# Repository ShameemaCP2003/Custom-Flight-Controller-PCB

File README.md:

# Custom Flight Controller PCB

Open-source STM32-based flight controller designed in KiCad for PX4 and ArduPilot-compatible UAV platforms.

---

## Overview

This project is a custom flight controller developed from scratch as a learning and engineering exercise in embedded hardware design, sensor integration, power management, and PCB development.

The design is inspired by modern flight controller architectures and incorporates a high-performance STM32 microcontroller, onboard inertial sensors, environmental sensing, multiple communication interfaces, and PWM outputs for UAV control applications.

---

## Features

- STM32F446RET6 ARM Cortex-M4 MCU
- ICM-42670-P 6-Axis IMU
- BMP390 Barometric Pressure Sensor
- USB Type-C Interface
- CAN Bus Support
- Multiple UART Interfaces
- Dual SPI Interfaces
- ADC Inputs
- GPIO Expansion
- 6 Servo/PWM Outputs
- SWD Programming Interface
- Onboard 3.3V Regulation
- Power Protection Circuitry

---

## Hardware Specifications

| Component | Part Number |
|------------|------------|
| MCU | STM32F446RET6 |
| IMU | ICM-42670-P |
| Barometer | BMP390 |
| Voltage Regulator | SPX3819 |
| Crystal | 3.2mm × 2.5mm |
| USB Interface | USB Type-C |

---

## Communication Interfaces

| Interface | Quantity |
|------------|----------|
| CAN Bus | 1 |
| UART | 3 |
| SPI | 2 |
| ADC | 2 |
| GPIO Input | 1 |
| GPIO Output | 2 |

---

## PWM Outputs

| Output |
|----------|
| Servo 1 |
| Servo 2 |
| Servo 3 |
| Servo 4 |
| Servo 5 |
| Servo 6 |

---

## PCB Statistics

| Parameter | Value |
|------------|---------|
| Layers | 2 |
| Nets | 79 |
| Pads | 291 |
| Vias | 297 |
| Unrouted Nets | 0 |
| ERC Status | Passed |
| DRC Status | Passed |

---

## Design Workflow

1. Requirements Definition
2. Component Selection
3. Schematic Design
4. ERC Validation
5. PCB Placement
6. PCB Routing
7. Ground Plane Implementation
8. DRC Verification
9. Prototype Preparation

---

## Current Status

- ✅ Schematic Complete
- ✅ PCB Layout Complete
- ✅ ERC Passed
- ✅ DRC Passed
- ⏳ Prototype Manufacturing Pending
- ⏳ Hardware Bring-Up Pending
- ⏳ PX4 Integration Pending

---

## Future Improvements

Planned future revisions include:

- Dual redundant IMU architecture
- SD card logging
- Additional CAN interfaces
- GPS connector
- Battery management system
- Power monitoring enhancements
- 4-layer PCB revision
- PX4 board support package
- ArduPilot board support package

---

## Repository Structure

hardware/
├── schematic/
└── pcb/

docs/
└── images/

firmware/

---

## Acknowledgements

This project was created as a learning and engineering exercise in custom flight controller design.

The development process was heavily influenced by the open-source embedded systems community, including the educational content and flight controller development resources shared by Timothy Kowalski.

## References

This project was developed with the help of open-source resources and educational content.

### Timothy Kowalski

Special thanks to Timothy Kowalski for sharing detailed flight controller development content and open-source hardware resources.

Reference Project:
- [Custom Flight Controller](https://github.com/HomeGliders/FCV2)

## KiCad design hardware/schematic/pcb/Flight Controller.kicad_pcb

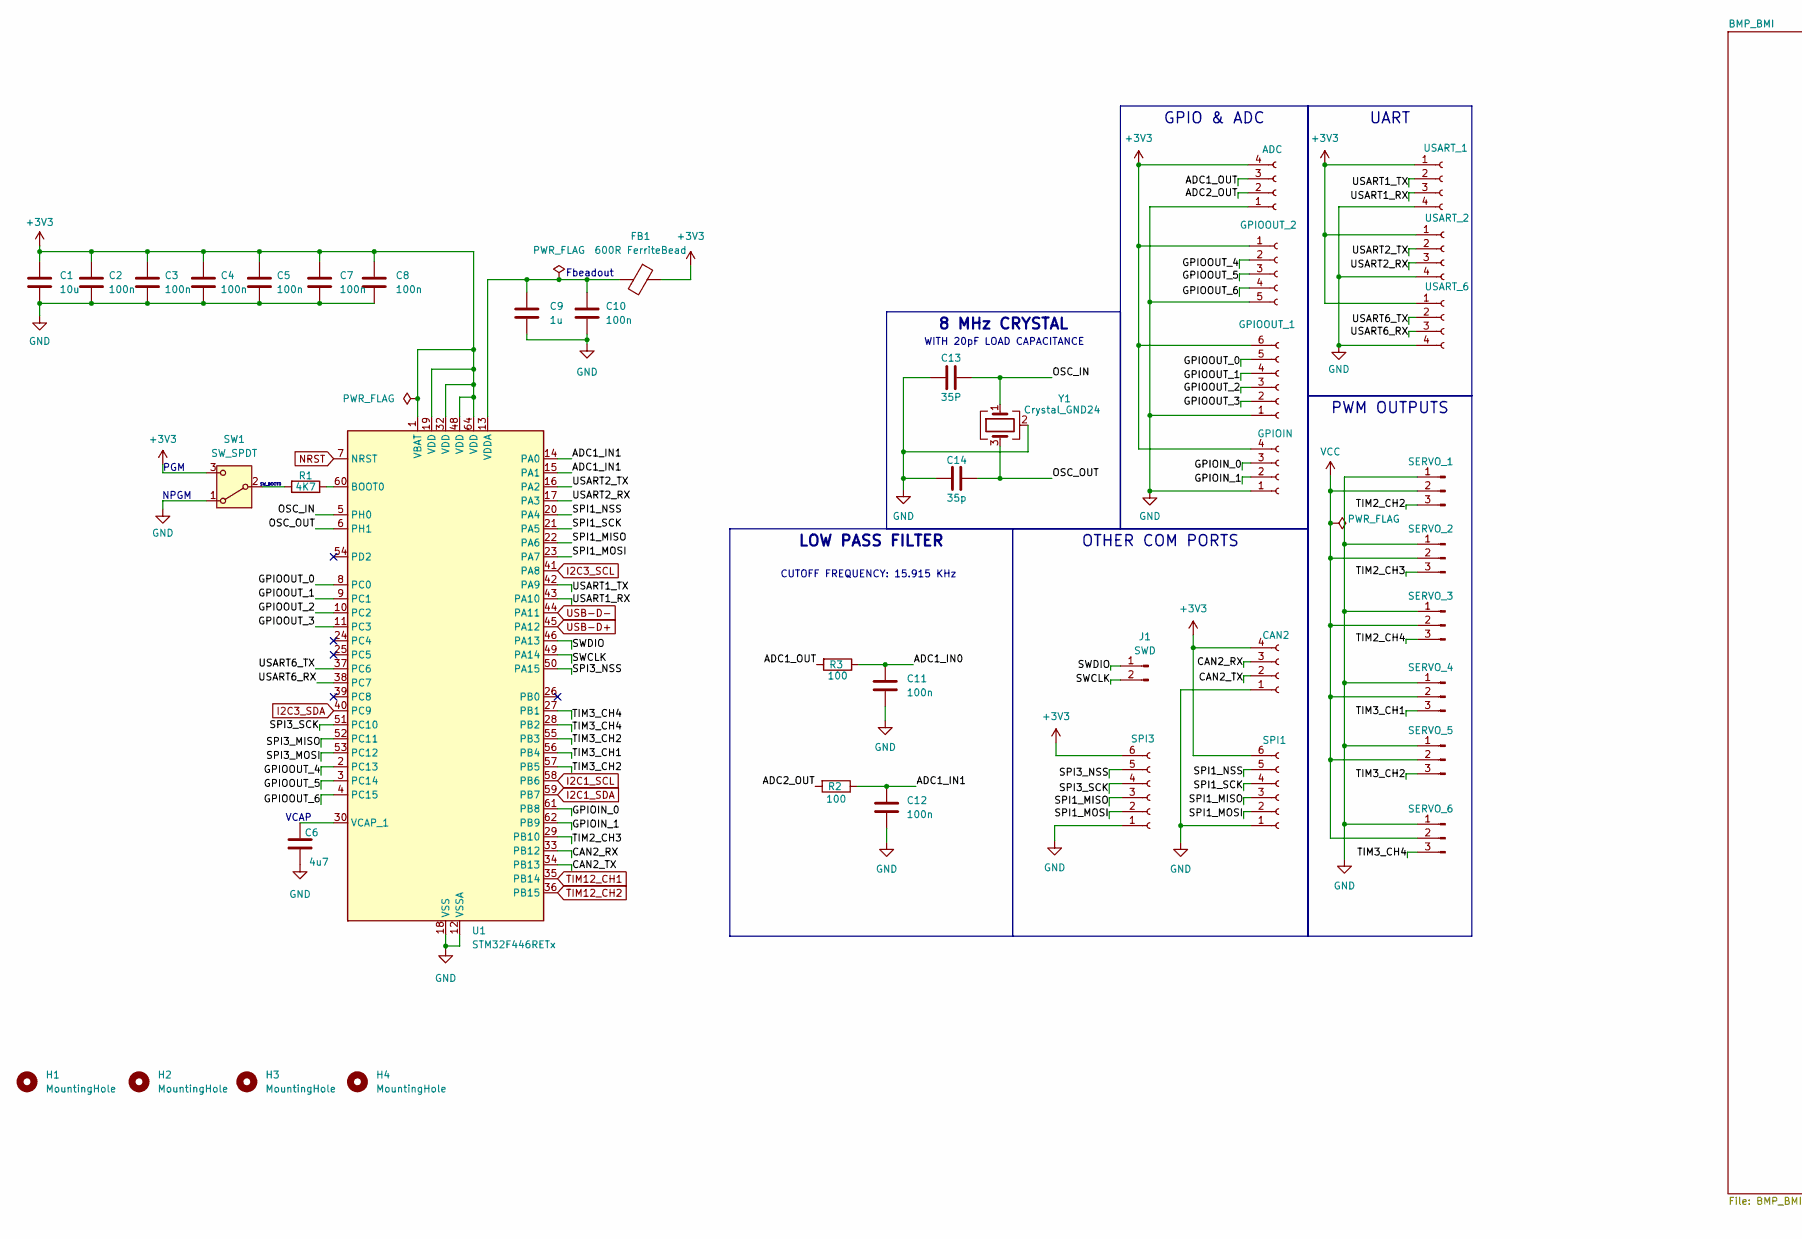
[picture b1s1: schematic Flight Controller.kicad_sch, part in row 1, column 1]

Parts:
C1: 10u; C_0603_1608Metric
C2, C3, C4, C5, C7, C8, C10, C11, C12: 100n; C_0402_1005Metric
C6: 4u7; C_0603_1608Metric
C9: 1u; C_0402_1005Metric
C13: 35P; C_0402_1005Metric
C14: 35p; C_0402_1005Metric
FB1: 600R FerriteBead; L_0603_1608Metric
H1, H2, H3, H4: MountingHole; MountingHole_2.2mm_M2
J1: SWD; PinSocket_1x02_P2.54mm_Vertical
J2: SPI3; PinHeader_1x06_P2.54mm_Vertical
J3: ADC; PinHeader_1x04_P2.54mm_Vertical
J4: GPIOOUT_2; PinHeader_1x05_P2.54mm_Vertical
J5: GPIOOUT_1; PinHeader_1x06_P2.54mm_Vertical
J6: GPIOIN; PinHeader_1x04_P2.54mm_Vertical
J7: CAN2; PinHeader_1x04_P2.54mm_Vertical
J8: SPI1; PinHeader_1x06_P2.54mm_Vertical
J9: USART_1; PinHeader_1x04_P2.54mm_Vertical
J10: USART_2; PinHeader_1x04_P2.54mm_Vertical
J11: USART_6; PinHeader_1x04_P2.54mm_Vertical
J12: SERVO_1; PinHeader_1x03_P2.54mm_Vertical
J13: SERVO_2; PinHeader_1x03_P2.54mm_Vertical
J14: SERVO_3; PinHeader_1x03_P2.54mm_Vertical
J15: SERVO_4; PinHeader_1x03_P2.54mm_Vertical
J16: SERVO_5; PinHeader_1x03_P2.54mm_Vertical
J17: SERVO_6; PinHeader_1x03_P2.54mm_Vertical
R1: 4K7; R_0402_1005Metric
R2, R3: 100; R_0402_1005Metric
SW1: SW_SPDT; SW_SPDT_PCM12
U1: STM32F446RETx; LQFP-64_10x10mm_P0.5mm
Y1: Crystal_GND24; Crystal_SMD_3225-4Pin_3.2x2.5mm

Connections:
+3V3: C1.1, C2.1, C3.1, C4.1, C5.1, C7.1, C8.1, FB1.1, J2.6, J3.4, J4.1, J5.6, J6.4, J7.4, J8.6, J9.1, J10.1, J11.1, SW1.3 (C), U1.1 (VBAT), U1.19 (VDD), U1.32 (VDD), U1.48 (VDD), U1.64 (VDD)
/ADC1_IN0: C11.1, R3.1
/ADC1_IN1: C12.1, R2.1, U1.14 (PA0), U1.15 (PA1)
/ADC1_OUT: J3.3, R3.2
/ADC2_OUT: J3.2, R2.2
/CAN2_RX: J7.3, U1.33 (PB12)
/CAN2_TX: J7.2, U1.34 (PB13)
/GPIOIN_0: J6.3, U1.61 (PB8)
/GPIOIN_1: J6.2, U1.62 (PB9)
/GPIOOUT_0: J5.5, U1.8 (PC0)
/GPIOOUT_1: J5.4, U1.9 (PC1)
/GPIOOUT_2: J5.3, U1.10 (PC2)
/GPIOOUT_3: J5.2, U1.11 (PC3)
/GPIOOUT_4: J4.2, U1.2 (PC13)
/GPIOOUT_5: J4.3, U1.3 (PC14)
/GPIOOUT_6: J4.4, U1.4 (PC15)
/OSC_IN: C13.1, U1.5 (PH0), Y1.1
/OSC_OUT: C14.1, U1.6 (PH1), Y1.3
/SPI1_MISO: J2.3, J8.3, U1.22 (PA6)
/SPI1_MOSI: J2.2, J8.2, U1.23 (PA7)
/SPI1_NSS: J8.5, U1.20 (PA4)
/SPI1_SCK: J8.4, U1.21 (PA5)
/SPI3_MISO: U1.52 (PC11)
/SPI3_MOSI: U1.53 (PC12)
/SPI3_NSS: J2.5, U1.50 (PA15)
/SPI3_SCK: J2.4, U1.51 (PC10)
/SWCLK: J1.2, U1.49 (PA14)
/SWDIO: J1.1, U1.46 (PA13)
/TIM2_CH2: J12.3
/TIM2_CH3: J13.3, U1.29 (PB10)
/TIM2_CH4: J14.3
/TIM3_CH1: J15.3, U1.56 (PB4)
/TIM3_CH2: J16.3, U1.55 (PB3), U1.57 (PB5)
/TIM3_CH4: J17.3, U1.27 (PB1), U1.28 (PB2)
/USART1_RX: J9.3, U1.43 (PA10)
/USART1_TX: J9.2, U1.42 (PA9)
/USART2_RX: J10.3, U1.17 (PA3)
/USART2_TX: J10.2, U1.16 (PA2)
/USART6_RX: J11.3, U1.38 (PC7)
/USART6_TX: J11.2, U1.37 (PC6)
GND: C1.2, C2.2, C3.2, C4.2, C5.2, C6.2, C7.2, C8.2, C9.2, C10.2, C11.2, C12.2, C13.2, C14.2, J2.1, J3.1, J4.5, J5.1, J6.1, J7.1, J8.1, J9.4, J10.4, J11.4, J12.1, J13.1, J14.1, J15.1, J16.1, J17.1, SW1.1 (A), U1.12 (VSSA), U1.18 (VSS), U1.31 (VSS), U1.47 (VSS), U1.63 (VSS), Y1.2 (G), Y1.4 (G); also elsewhere on the board
I2C1_SCL: U1.58 (PB6); also elsewhere on the board
I2C1_SDA: U1.59 (PB7); also elsewhere on the board
I2C3_SCL: U1.41 (PA8); also elsewhere on the board
I2C3_SDA: U1.40 (PC9); also elsewhere on the board
NRST: U1.7 (NRST); also elsewhere on the board
unnamed: R1.2, SW1.2 (B)
unnamed: R1.1, U1.60 (BOOT0)
unnamed: C6.1, U1.30 (VCAP_1)
unnamed: C9.1, C10.1, FB1.2, U1.13 (VDDA)
TIM12_CH1: U1.35 (PB14); also elsewhere on the board
TIM12_CH2: U1.36 (PB15); also elsewhere on the board
USB-D+: U1.45 (PA12); also elsewhere on the board
USB-D-: U1.44 (PA11); also elsewhere on the board
VCC: J12.2, J13.2, J14.2, J15.2, J16.2, J17.2

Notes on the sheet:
PGM
Fbeadout
CUTOFF FREQUENCY: 15.915 KHz
NPGM
WITH 20pF LOAD CAPACITANCE
VCAP
SW_BOOT0
GPIO & ADC
LOW PASS FILTER
OTHER COM PORTS
UART
8 MHz CRYSTAL
PWM OUTPUTS

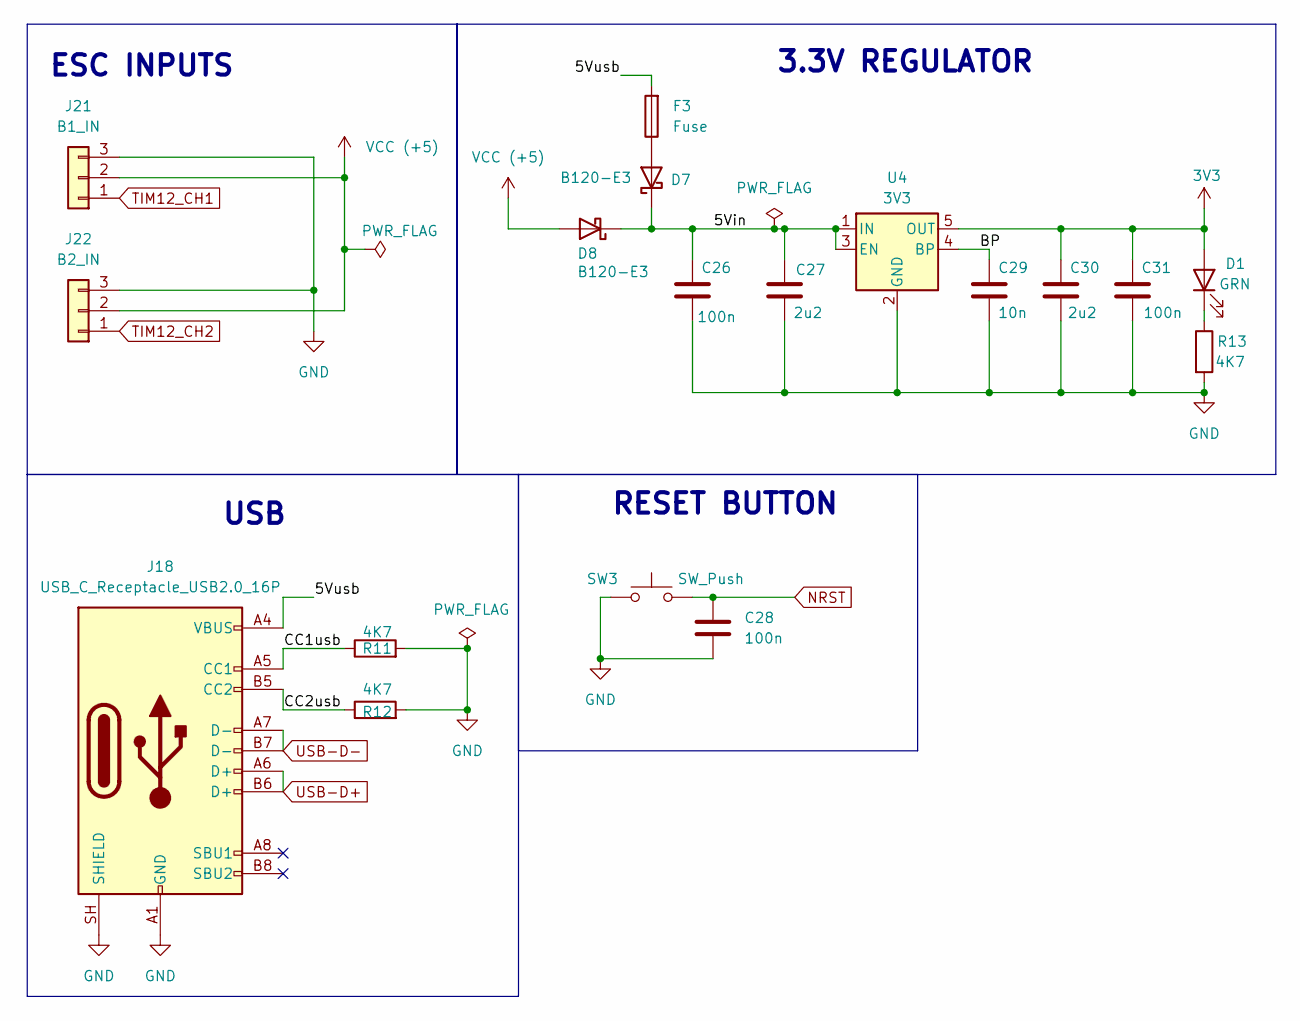
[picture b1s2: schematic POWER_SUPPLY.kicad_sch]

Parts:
C26, C28, C31: 100n; C_0402_1005Metric
C27, C30: 2u2; C_0603_1608Metric
C29: 10n; C_0402_1005Metric
D1: GRN; LED_0603_1608Metric
D7, D8: B120-E3; D_0603_1608Metric
F3: Fuse; Fuse_1206_3216Metric
J18: USB_C_Receptacle_USB2.0_16P; USB_C_Receptacle_XKB_U262-16XN-4BVC11
J21: B1_IN; PinHeader_1x03_P2.54mm_Vertical
J22: B2_IN; PinHeader_1x03_P2.54mm_Vertical
R11, R12, R13: 4K7; R_0402_1005Metric
SW3: SW_Push; SW_SPST_TL3342
U4: 3V3; SOT-23-5

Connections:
3V3: C30.1, C31.1, D1.2 (A), U4.5 (OUT); also elsewhere on the board
/POWER_SUPPLY/5Vin: C26.1, C27.1, D7.1 (K), D8.1 (K), U4.1 (IN), U4.3 (EN)
/POWER_SUPPLY/5Vusb: F3.2, J18.A4 (VBUS), J18.A9 (VBUS), J18.B4 (VBUS), J18.B9 (VBUS)
/POWER_SUPPLY/BP: C29.1, U4.4 (BP)
/POWER_SUPPLY/CC1usb: J18.A5 (CC1), R11.1
/POWER_SUPPLY/CC2usb: J18.B5 (CC2), R12.1
GND: C26.2, C27.2, C28.2, C29.2, C30.2, C31.2, J18.A1 (GND), J18.A12 (GND), J18.B1 (GND), J18.B12 (GND), J18.SH (SHIELD), J21.3, J22.3, R11.2, R12.2, R13.2, SW3.1, U4.2 (GND); also elsewhere on the board
NRST: C28.1, SW3.2; also elsewhere on the board
unnamed: D1.1 (K), R13.1
unnamed: D7.2 (A), F3.1
TIM12_CH1: J21.1; also elsewhere on the board
TIM12_CH2: J22.1; also elsewhere on the board
USB-D+: J18.A6 (D+), J18.B6 (D+); also elsewhere on the board
USB-D-: J18.A7 (D-), J18.B7 (D-); also elsewhere on the board
VCC (+5): D8.2 (A), J21.2, J22.2

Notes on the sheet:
RESET BUTTON
USB
ESC INPUTS
3.3V REGULATOR

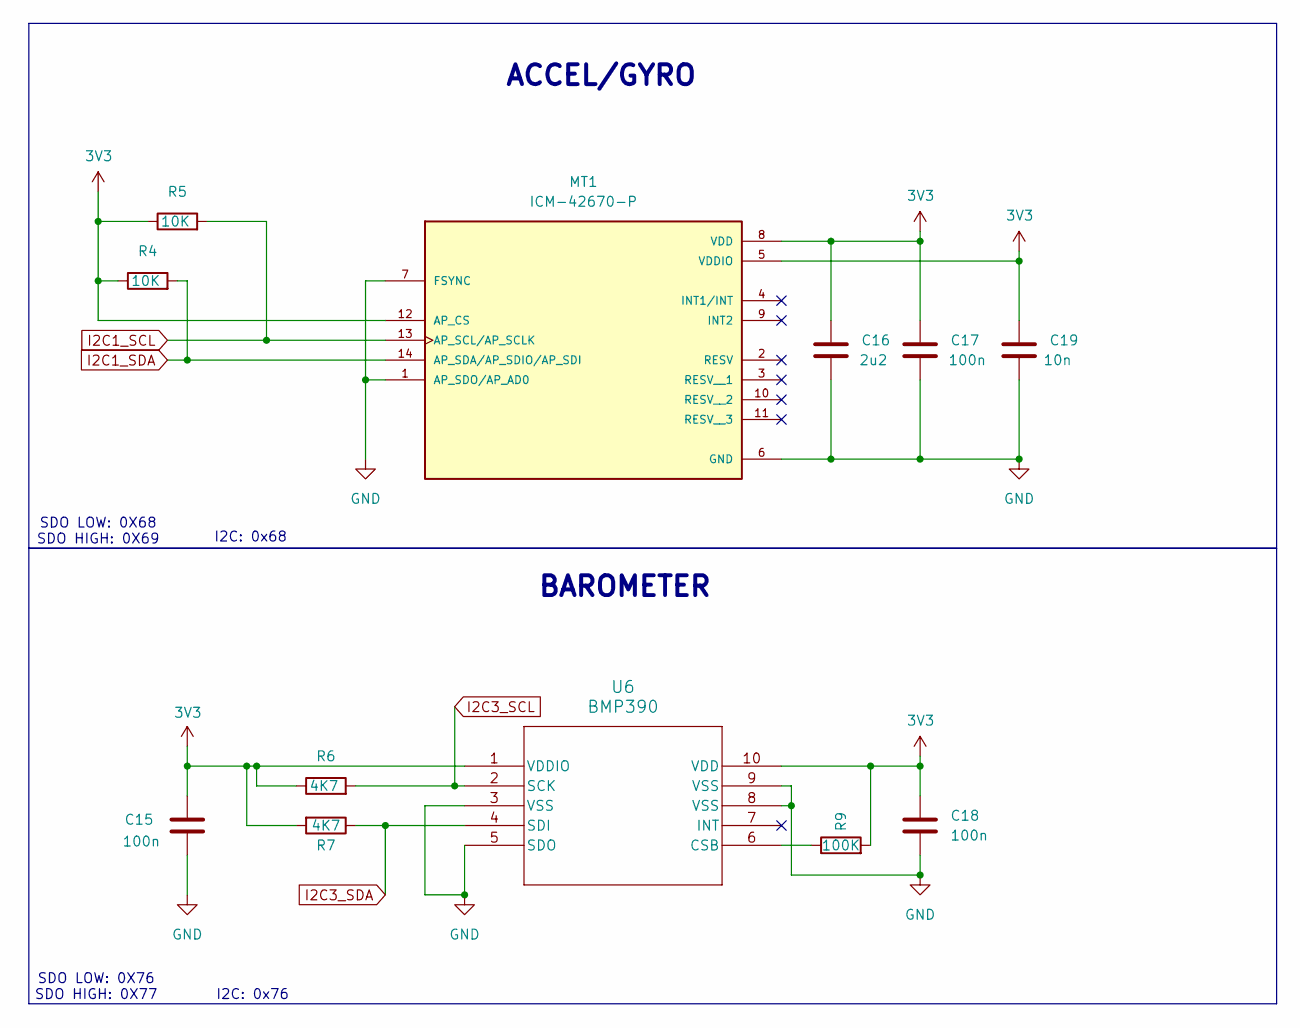
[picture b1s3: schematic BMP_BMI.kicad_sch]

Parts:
C15, C17, C18: 100n; C_0402_1005Metric
C16: 2u2; C_0603_1608Metric
C19: 10n; C_0402_1005Metric
MT1: ICM-42670-P; LGA-14_3x2.5mm_P0.5mm_LayoutBorder3x4y; PARTREV 1.1
R4, R5: 10K; R_0402_1005Metric
R6, R7: 4K7; R_0402_1005Metric
R9: 100K; R_0402_1005Metric
U6: BMP390; ST_HLGA-10_2x2mm_P0.5mm_LayoutBorder3x2y

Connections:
3V3: C15.1, C16.1, C17.1, C18.1, C19.1, MT1.5 (VDDIO), MT1.8 (VDD), MT1.12 (AP_CS), R4.1, R5.1, R6.1, R7.2, R9.2, U6.1 (VDDIO), U6.10 (VDD); also elsewhere on the board
GND: C15.2, C16.2, C17.2, C18.2, C19.2, MT1.1 (AP_SDO/AP_AD0), MT1.6 (GND), MT1.7 (FSYNC), U6.3 (VSS), U6.5 (SDO), U6.8 (VSS), U6.9 (VSS); also elsewhere on the board
I2C1_SCL: MT1.13 (AP_SCL/AP_SCLK), R5.2; also elsewhere on the board
I2C1_SDA: MT1.14 (AP_SDA/AP_SDIO/AP_SDI), R4.2; also elsewhere on the board
I2C3_SCL: R6.2, U6.2 (SCK); also elsewhere on the board
I2C3_SDA: R7.1, U6.4 (SDI); also elsewhere on the board
unnamed: R9.1, U6.6 (CSB)

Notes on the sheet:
SDO LOW: 0X76 SDO HIGH: 0X77
ACCEL/GYRO
I2C: 0x68
I2C: 0x76
SDO LOW: 0X68 SDO HIGH: 0X69
BAROMETER

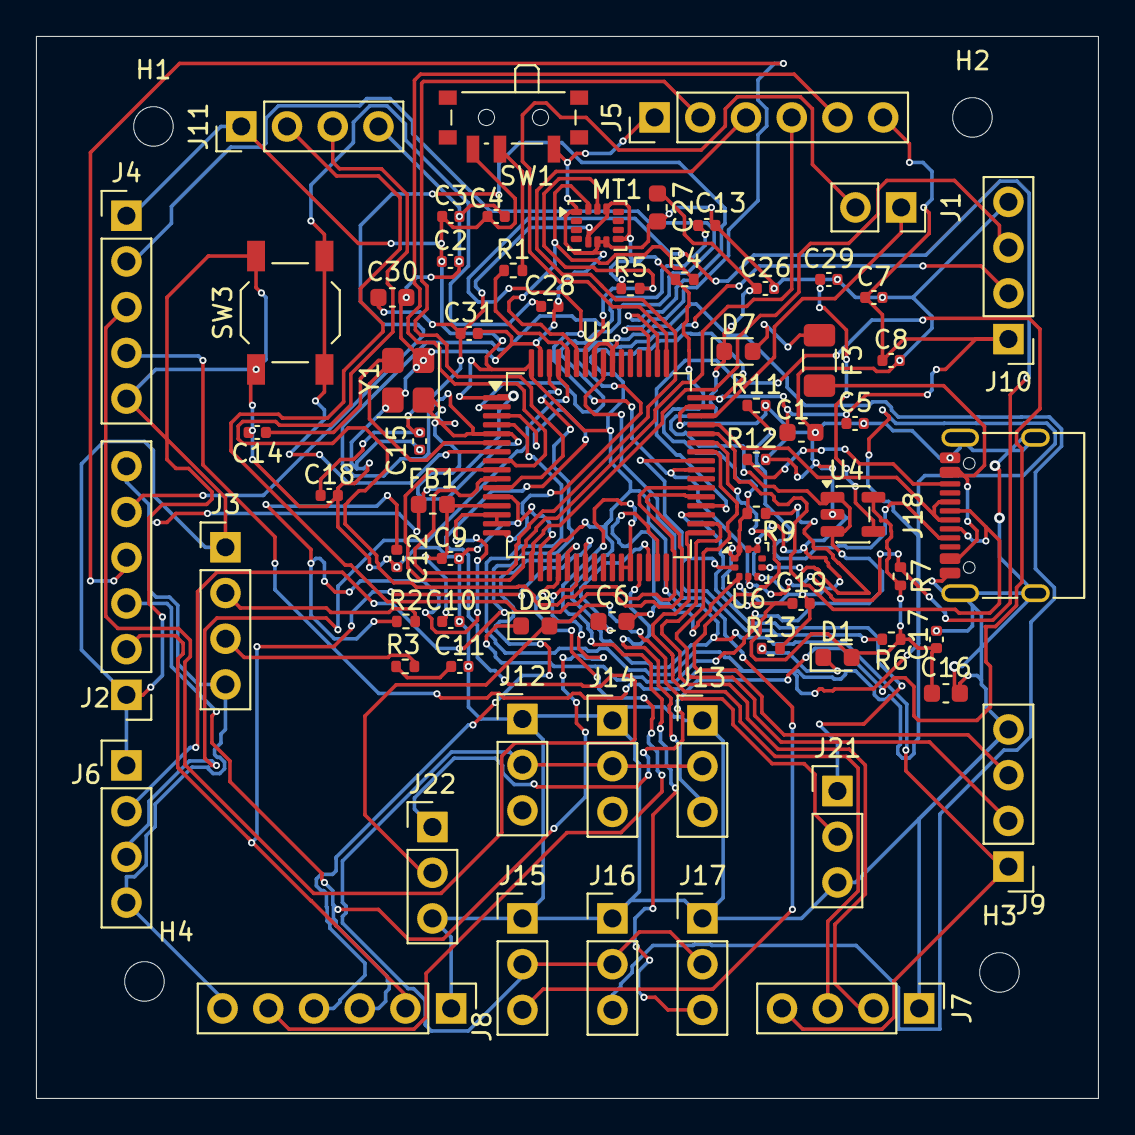
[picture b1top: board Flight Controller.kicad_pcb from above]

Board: 2 copper layers, 59.0 x 59.0 mm, 72 parts (0 on the bottom side), 61 nets.
